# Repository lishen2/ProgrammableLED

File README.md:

自动刹车灯
===============
自动刹车灯是一个小巧的电路板，在刹车减速时自动亮起。可以将其安装在自行车上，用于警示其他车辆和行人。自动刹车灯由电池供电并内置加速度传感器，因此无需额外连接其他线缆。使用两节5号电池时，设计待机时间为一年以上(待机功耗66微安)，基本可以实现永不关机，即装即忘。项目命名为“ProgrammableLED”是最初的初衷，现在已经简化为自动刹车等了，功能简化体验更优。

特性
--------
* 体积2.8cm * 5.5cm(PCB尺寸)。
* 自动识别减速刹车。
* 停车自动休眠，设计待机时间一年以上。
* 软硬件设计开源。

应用
-------
* 自行车灯，提高车辆夜间识别度，增强安全性。

硬件资源
--------
* STM32F103C8T处理器
* 两个全彩LED灯，两个红色LED（1206）
* 加速度传感器ADXL345
* 一个三线串口
* 一个三线SWD接口

当前进度
--------
20140217: 第一版PCB制作完成.                     
20140220: 编写代码，STM32的USB驱动示例代码很烂，作为程序员不忍直视。              
20140319: 放弃使用USB口，原因是USB驱动比较复杂一直没有调试成功。                  
20140329: 第二版PCB制作完成，放弃USB接口，增加加速度传感器ADXL234和升压电路（保证LED亮度一致）                    
20140410：还在编写软件，放弃编程功能，仅留下刹车灯功能。                   
20140506：基本功能正常，正在优化功耗。
20140515：耗降到66微安，正在调整对加速度数值的处理。
20140601：加速度传感器参数调整完毕，经过几周实测，效果还不错。

开发博客
--------
<http://blog.sina.com.cn/lgeek>

Automatic Break Light
===============
Automatic Break Light is a small circuit board, it can automatically light up when decelerate. It can installed on a bicycle to caution other bicycle,  vehicle and people. Automatic Break Light has an accelerate sensor on board, so it will work without additional sensor or wire. It use two AA battery as power supply, designed to work at least 12 month(Standby power consumption is 66 uA). You no longer need to manually shut it down, and you can forget it after install. The project name "ProgrammableLED" is the original idea, but now it has enolved into "Automatic Break Light". Fewer functions, better experience.

Design feature
--------------
* size 2.8cm * 5.5cm(PCB size).
* recognize decelerate.
* automatic sleep when stop, standby lifetime more than 12 month.
* open source on both software and hardware.

Application
-----------
* Bicycle light, improve identification at night.

Hardware
--------
* STM32F103C8T MCU
* 2 RGB LED, 2 red LED
* ADXL345 acceleration sensor
* 1 USART port
* 1 SWD

Current progress
---------------
20140217: Finished first PCB.                
20140220: Working on the code, STM32's USB Driver is horrible.            
20140319: Abandon USB port, too complicated.         
20140329: Finished second PCB, abandon USB port, add ADXL234 sensor, and boost circuit.           
20140410：Still working on software, just break light.            
20140506：Barely work, working on reduce power consumption.
20140515：Standby power consumption down to 66 mA, Adjusting processing logic about acceleration value.
20140601: Finish adjusting logic. After several weeks trail, it's basically good.

Development blog
---------------
<http://lsgeek.blogspot.com>

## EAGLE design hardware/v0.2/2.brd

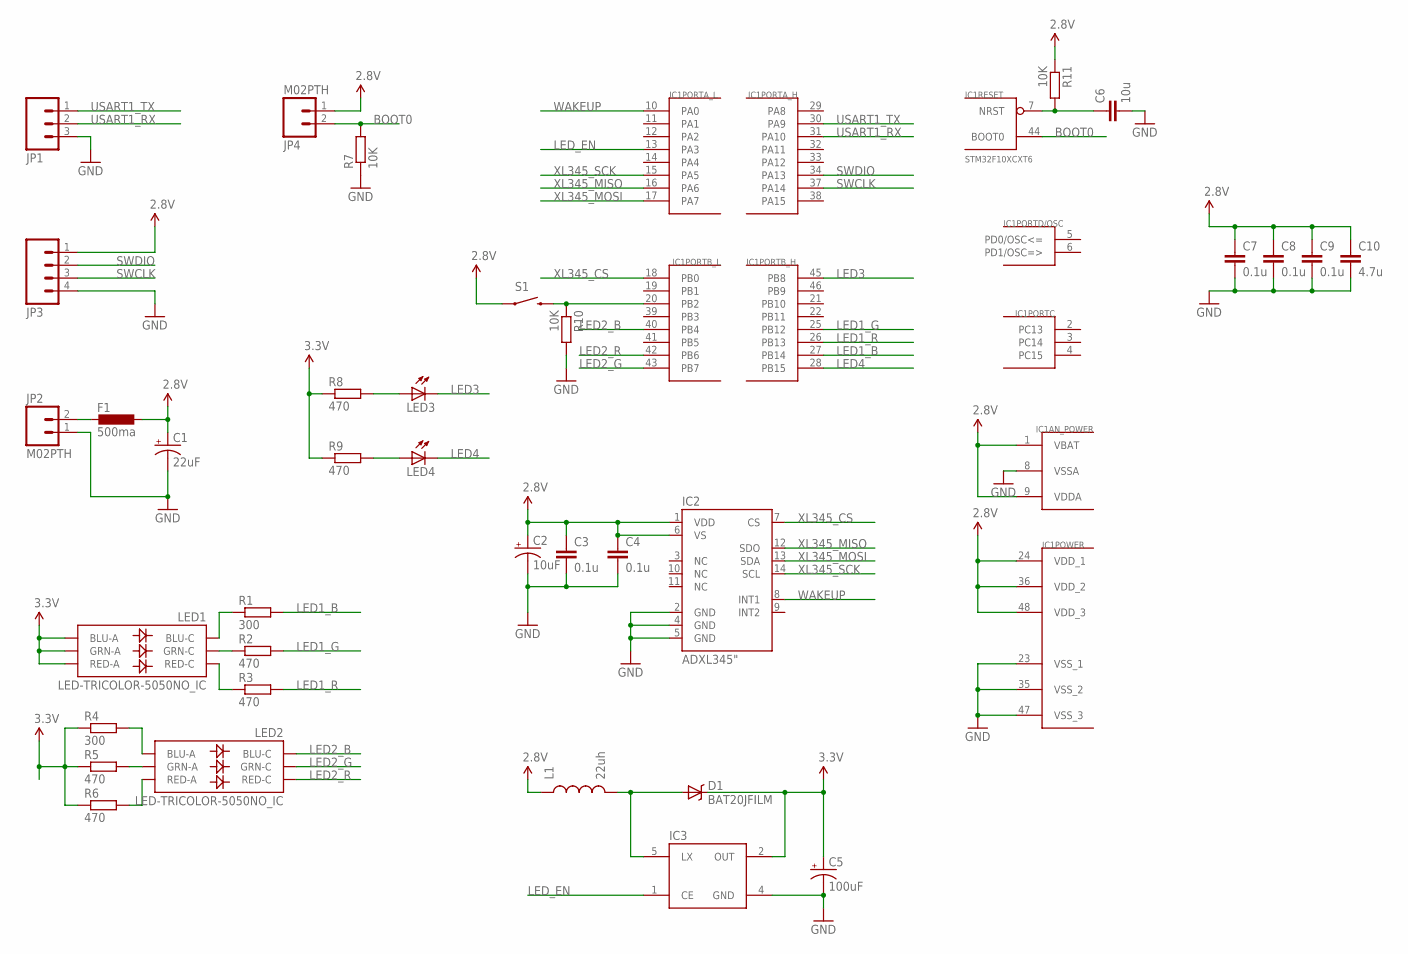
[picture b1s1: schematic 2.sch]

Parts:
C1: 22uF; EIA3216
C2: 10uF; EIA3216
C3, C4, C7, C8, C9: 0.1u; C0603K
C5: 100uF; EIA3528
C6: 10u; C0603K
C10: 4.7u; C0603K
D1: BAT20JFILM; SOD-323
F1: 500ma; L2012C
IC1: STM32F10XCXT6; TQFP48
IC2: ADXL345"; ADXL3451:1
IC3: BL8530-XX2_RN; SOT23-5
JP1: M03PTH; 1X03
JP2, JP4: M02PTH; 1X02
JP3: M04PTH; 1X04
L1: 22uh; VLF4012A
LED1, LED2: LED-TRICOLOR-5050NO_IC; LED-TRICOLOR-5050
LED3, LED4: LED1206; LED-1206
R1, R4: 300; R0603
R2, R3, R5, R6, R8, R9: 470; R0603
R7, R10, R11: 10K; R0603
S1: SWITCH-MOMENTARY-2-SMD-1101NE; TACTILE-SWITCH-1101NE

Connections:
2.8V: C1.A (+), C2.A (+), C3.1, C4.1, C7.1, C8.1, C9.1, C10.1, F1.1, IC1.1 (VBAT), IC1.9 (VDDA), IC1.24 (VDD_1), IC1.36 (VDD_2), IC1.48 (VDD_3), IC2.1 (VDD), IC2.6 (VS), JP3.1, JP4.1, L1.P$1 (1), R11.1, S1.P$1 (1)
3.3V: C5.A (+), D1.1 (C), IC3.2 (OUT), LED1.1 (GRN-A), LED1.2 (RED-A), LED1.3 (BLU-A), R4.1, R5.1, R6.1, R8.1, R9.1
BOOT0: IC1.44 (BOOT0), JP4.2, R7.2
GND: C1.C (-), C2.C (-), C3.2, C4.2, C5.C (-), C6.2, C7.2, C8.2, C9.2, C10.2, IC1.8 (VSSA), IC1.23 (VSS_1), IC1.35 (VSS_2), IC1.47 (VSS_3), IC2.2 (GND), IC2.4 (GND), IC2.5 (GND), IC3.4 (GND), JP1.3, JP2.1, JP3.4, R7.1, R10.2
LED1_B: IC1.27 (PB14), R1.2
LED1_G: IC1.25 (PB12), R2.2
LED1_R: IC1.26 (PB13), R3.2
LED2_B: IC1.40 (PB4), LED2.4 (BLU-C)
LED2_G: IC1.43 (PB7), LED2.6 (GRN-C)
LED2_R: IC1.42 (PB6), LED2.5 (RED-C)
LED3: IC1.45 (PB8), LED3.C
LED4: IC1.28 (PB15), LED4.C
LED_EN: IC1.13 (PA3), IC3.1 (CE)
unnamed: F1.2, JP2.2
unnamed: IC1.20 (PB2), R10.1, S1.P$2 (2)
unnamed: LED4.A, R9.2
unnamed: LED3.A, R8.2
unnamed: LED2.3 (BLU-A), R4.2
unnamed: LED1.6 (GRN-C), R2.1
unnamed: LED2.2 (RED-A), R6.2
unnamed: LED1.4 (BLU-C), R1.1
unnamed: LED2.1 (GRN-A), R5.2
unnamed: LED1.5 (RED-C), R3.1
unnamed: D1.2 (A), IC3.5 (LX), L1.P$2 (2)
RESET: C6.1, IC1.7 (NRST), R11.2
SWCLK: IC1.37 (PA14), JP3.3
SWDIO: IC1.34 (PA13), JP3.2
USART1_RX: IC1.31 (PA10), JP1.2
USART1_TX: IC1.30 (PA9), JP1.1
WAKEUP: IC1.10 (PA0), IC2.8 (INT1)
XL345_CS: IC1.18 (PB0), IC2.7 (CS)
XL345_MISO: IC1.16 (PA6), IC2.12 (SDO)
XL345_MOSI: IC1.17 (PA7), IC2.13 (SDA)
XL345_SCK: IC1.15 (PA5), IC2.14 (SCL)

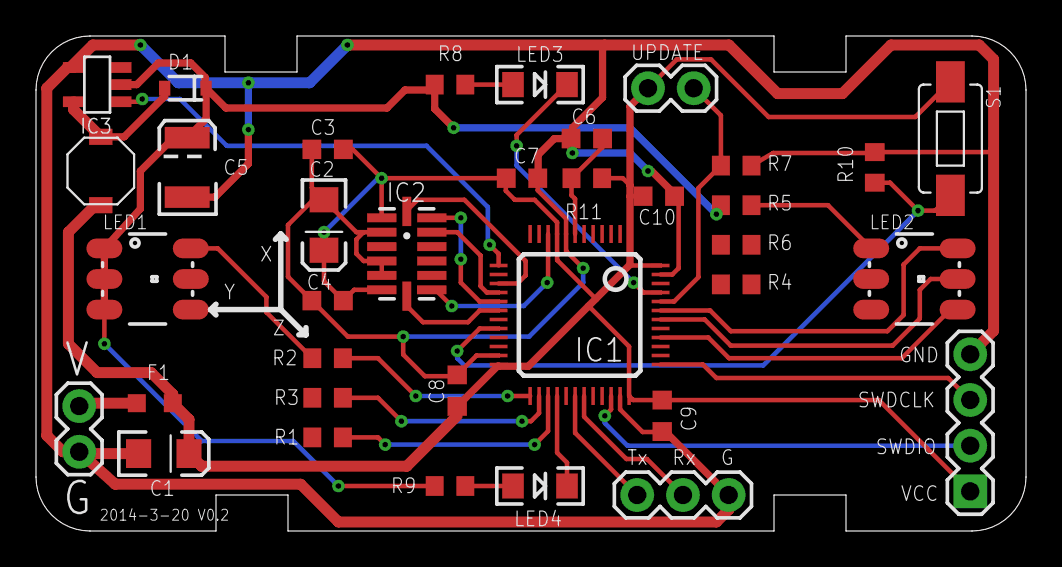
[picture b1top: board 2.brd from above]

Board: 2 copper layers, 55.0 x 27.5 mm, 36 parts (0 on the bottom side), 34 nets.

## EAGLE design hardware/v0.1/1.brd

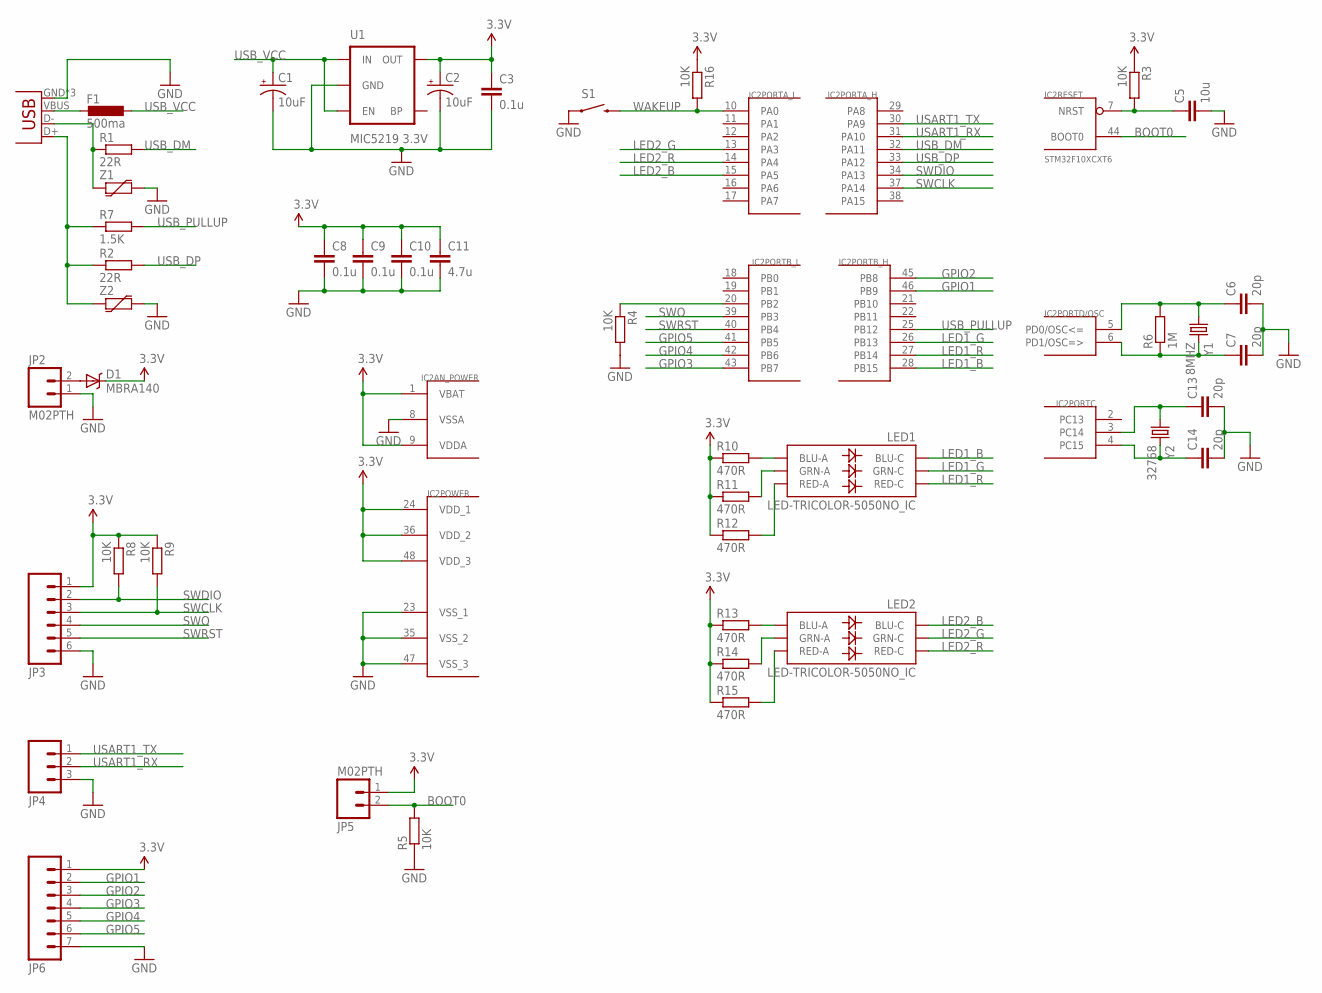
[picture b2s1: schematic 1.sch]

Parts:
C1, C2: 10uF; EIA3216
C3, C8, C9, C10: 0.1u; C0603K
C5: 10u; C0603K
C6, C7, C13, C14: 20p; C0603K
C11: 4.7u; C0603K
D1: MBRA140; SMA-DIODE
F1: 500ma; L2012C
IC2: STM32F10XCXT6; TQFP48
JP1: USB-MICROB
JP2, JP5: M02PTH; 1X02
JP3: M06SIP; 1X06
JP4: M03PTH; 1X03
JP6: M07; 1X07
LED1, LED2: LED-TRICOLOR-5050NO_IC; LED-TRICOLOR-5050
R1, R2: 22R; R0603
R3, R4, R5, R8, R9, R16: 10K; R0603
R6: 1M; R0603
R7: 1.5K; R0603
R10, R11, R12, R13, R14, R15: 470R; R0603
S1: SWITCH-MOMENTARY-2SMD-4; TACTILE_SWITCH_TALL
U1: MIC5219 3.3V; SOT23-5
Y1: 8MHZ; CRYSTAL-SMD-5X3
Y2: 32768; CRYSTAL-32KHZ-SMD_EPSON_MC146
Z1, Z2: VARISTOR-0603; 0603-RES

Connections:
3.3V: C2.A (+), C3.1, C8.1, C9.1, C10.1, C11.1, D1.C, IC2.1 (VBAT), IC2.9 (VDDA), IC2.24 (VDD_1), IC2.36 (VDD_2), IC2.48 (VDD_3), JP3.1, JP5.1, JP6.1, R3.1, R8.1, R9.1, R10.1, R11.1, R12.1, R13.1, R14.1, R15.1, R16.1, U1.5 (OUT)
BOOT0: IC2.44 (BOOT0), JP5.2, R5.2
GND: C1.C (-), C2.C (-), C3.2, C5.2, C6.2, C7.2, C8.2, C9.2, C10.2, C11.2, C13.2, C14.2, IC2.8 (VSSA), IC2.23 (VSS_1), IC2.35 (VSS_2), IC2.47 (VSS_3), JP1.GND, JP1.MT1 (GND), JP1.MT2 (GND), JP2.1, JP3.6, JP4.3, JP6.7, R4.2, R5.1, S1.A2 (1), U1.2 (GND), Z1.2, Z2.2
GPIO1: IC2.46 (PB9), JP6.2
GPIO2: IC2.45 (PB8), JP6.3
GPIO3: IC2.43 (PB7), JP6.4
GPIO4: IC2.42 (PB6), JP6.5
GPIO5: IC2.41 (PB5), JP6.6
LED1_B: IC2.28 (PB15), LED1.4 (BLU-C)
LED1_G: IC2.26 (PB13), LED1.6 (GRN-C)
LED1_R: IC2.27 (PB14), LED1.5 (RED-C)
LED2_B: IC2.15 (PA5), LED2.4 (BLU-C)
LED2_G: IC2.13 (PA3), LED2.6 (GRN-C)
LED2_R: IC2.14 (PA4), LED2.5 (RED-C)
unnamed: D1.A, JP2.2
unnamed: IC2.20 (PB2), R4.1
unnamed: JP1.D-, R1.1, Z1.1
unnamed: JP1.D+, R2.1, R7.1, Z2.1
unnamed: C6.1, IC2.5 (PD0/OSC<=), R6.2, Y1.1
unnamed: C7.1, IC2.6 (PD1/OSC=>), R6.1, Y1.3 (2)
unnamed: LED1.3 (BLU-A), R10.2
unnamed: F1.2, JP1.VBUS
unnamed: LED1.1 (GRN-A), R11.2
unnamed: LED1.2 (RED-A), R12.2
unnamed: LED2.3 (BLU-A), R13.2
unnamed: LED2.1 (GRN-A), R14.2
unnamed: LED2.2 (RED-A), R15.2
unnamed: C13.1, IC2.3 (PC14), Y2.P$2 (1)
unnamed: C14.1, IC2.4 (PC15), Y2.P$1 (2)
RESET: C5.1, IC2.7 (NRST), R3.2
SWCLK: IC2.37 (PA14), JP3.3, R9.2
SWDIO: IC2.34 (PA13), JP3.2, R8.2
SWO: IC2.39 (PB3), JP3.4
SWRST: IC2.40 (PB4), JP3.5
USART1_RX: IC2.31 (PA10), JP4.2
USART1_TX: IC2.30 (PA9), JP4.1
USB_DM: IC2.32 (PA11), R1.2
USB_DP: IC2.33 (PA12), R2.2
USB_PULLUP: IC2.25 (PB12), R7.2
USB_VCC: C1.A (+), F1.1, U1.1 (IN), U1.3 (EN)
WAKEUP: IC2.10 (PA0), R16.2, S1.B2 (2)

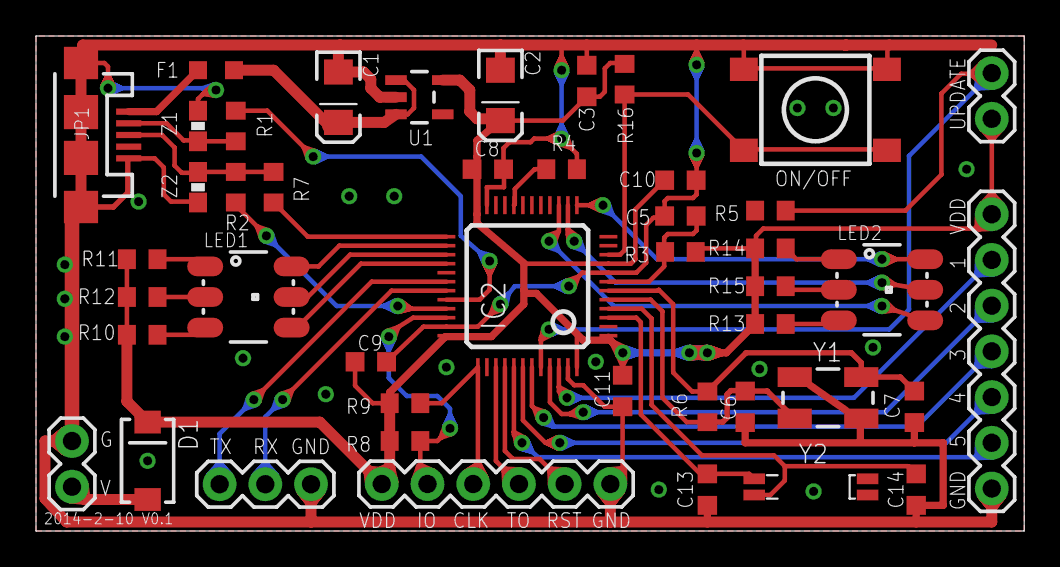
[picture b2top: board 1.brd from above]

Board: 2 copper layers, 54.9 x 27.5 mm, 45 parts (0 on the bottom side), 41 nets.

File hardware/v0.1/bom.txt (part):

Partlist exported from C:/Documents and Settings/Administrator/eagle/SmartLED/1.sch at 2014-2-13 17:03:51

Part Value                   Device                  Package                       Description                                                                         PROD_ID    VALUE       
C1   10uF                    10UF-TANT               EIA3216                       10uF Tantalum SMT                                                                   CAP-00811  10uF        
C2   10uF                    10UF-TANT               EIA3216                       10uF Tantalum SMT                                                                   CAP-00811  10uF        
C3   0.1u                    C-EUC0603K              C0603K                        CAPACITOR, European symbol                                                                                 
C5   10u                     C-EUC0603K              C0603K                        CAPACITOR, European symbol                                                                                 
C6   20p                     C-EUC0603K              C0603K                        CAPACITOR, European symbol                                                                                 
C7   20p                     C-EUC0603K              C0603K                        CAPACITOR, European symbol                                                                                 
C8   0.1u                    C-EUC0603K              C0603K                        CAPACITOR, European symbol                                                                                 
C9   0.1u                    C-EUC0603K              C0603K                        CAPACITOR, European symbol                                                                                 
C10  0.1u                    C-EUC0603K              C0603K                        CAPACITOR, European symbol                                                                                 
C11  4.7u                    C-EUC0603K              C0603K                        CAPACITOR, European symbol                                                                                 
C13  20p                     C-EUC0603K              C0603K                        CAPACITOR, European symbol                                                                                 
C14  20p                     C-EUC0603K              C0603K                        CAPACITOR, European symbol                                                                                 
D1   MBRA140                 MBRA140                 SMA-DIODE                     40V, 1A Schottky rectifier                                                          DIO-08053              
F1   500ma                   L-EUL2012C              L2012C                        INDUCTOR, European symbol                                                                                  
IC2  STM32F10XCXT6           STM32F10XCXT6           TQFP48                        ST STM32F101/103 48pin LQFP                                                                                
JP1  USB-MICROB              USB-MICROB              USB-MICROB                    USB Connectors                                                                      CONN-09505             
JP2  M02PTH                  M02PTH                  1X02                          Standard 2-pin 0.1" header. Use with                                                                       
JP3                          M06SIP                  1X06                          Header 6                                                                                                   
JP4                          M03PTH                  1X03                          Header 3                                                                                                   
JP5  M02PTH                  M02PTH                  1X02                          Standard 2-pin 0.1" header. Use with                                                                       
JP6                          M07                     1X07                          Header 7                                                                                                   
LED1 LED-TRICOLOR-5050NO_IC  LED-TRICOLOR-5050NO_IC  LED-TRICOLOR-5050                                                                                                                        
LED2 LED-TRICOLOR-5050NO_IC  LED-TRICOLOR-5050NO_IC  LED-TRICOLOR-5050                                                                                                                        
R1   22R                     R-EU_R0603              R0603                         RESISTOR, European symbol                                                                                  
R2   22R                     R-EU_R0603              R0603                         RESISTOR, European symbol                                                                                  
R3   10K                     R-EU_R0603              R0603                         RESISTOR, European symbol                                                                                  
R4   10K                     R-EU_R0603              R0603                         RESISTOR, European symbol                                                                                  
R5   10K                     R-EU_R0603              R0603                         RESISTOR, European symbol                                                                                  
R6   1M                      R-EU_R0603              R0603                         RESISTOR, European symbol                                                                                  
R7   1.5K                    R-EU_R0603              R0603                         RESISTOR, European symbol                                                                                  
R8   10K                     R-EU_R0603              R0603                         RESISTOR, European symbol                                                                                  
R9   10K                     R-EU_R0603              R0603                         RESISTOR, European symbol                                                                                  
R10  470R                    R-EU_R0603              R0603                         RESISTOR, European symbol                                                                                  
R11  470R                    R-EU_R0603              R0603                         RESISTOR, European symbol                                                                                  
R12  470R                    R-EU_R0603              R0603                         RESISTOR, European symbol                                                                                  
R13  470R                    R-EU_R0603              R0603                         RESISTOR, European symbol                                                                                  
R14  470R                    R-EU_R0603              R0603                         RESISTOR, European symbol                                                                                  
R15  470R                    R-EU_R0603              R0603                         RESISTOR, European symbol                                                                                  
R16  10K                     R-EU_R0603              R0603                         RESISTOR, European symbol                                                                                  
S1   SWITCH-MOMENTARY-2SMD-4 SWITCH-MOMENTARY-2SMD-4 TACTILE_SWITCH_TALL           Various NO switches- pushbuttons, reed, etc                                                                
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
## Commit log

2014-02-13 update readme, commit pcb design
2014-02-14 add jdbpcb cam file
2014-02-18 Update readme.md, fix a minor bug on PCB
2014-02-18 add software
2014-02-18 add image
2014-02-18 update image
2014-02-18 make readme display image
2014-02-20 Add test code
2014-02-20 更新进度
2014-02-21 update usb driver
2014-02-23 makeing standard request work
2014-02-24 continue development usb driver
2014-02-26 fix a bug, which is issued when recived multiple CTR interupts on EP0
2014-02-27 1. devided usb into usb library files and usb user files. 2.Begin to write scsi related code.
2014-03-02 writing usb driver
2014-03-04 implement SCSI inquery command, but have problems
2014-03-05 bulk endpoint get babble error when transmit data, not yet figure it out.
2014-03-12 add code read adxl345 chip
2014-03-14 write display control code
2014-03-16 add version 2 pcb desgin
2014-03-16 add xl345 code and flash control
2014-03-17 modify pcb design
2014-03-18 test led pwm alg
2014-03-19 Updated V2 PCB design
2014-03-20 update PCB design
2014-03-20 nearly finish PCB design
2014-03-24 finish version 0.2 pcb design
2014-03-26 testing flash display sequence
2014-03-27 20140327
2014-03-31 temp 20140331
2014-03-31 temporary
2014-04-02 update xl345 code
2014-04-03 update xl345
2014-04-07 adapt new hardware
2014-04-08 temp
2014-04-09 ACC now work properly
2014-04-10 nearly finish
2014-04-10 add space
2014-04-10 correct compile error
2014-05-03 workable version 1
2014-05-04 update schematic for clearance
2014-05-05 reduce standby power
2014-05-05 improve power consumion
2014-05-06 update readme and image
2014-05-06 reduce power consumption
2014-05-06 achieve 66 uA standby power consumption
2014-05-08 improve break light sensitivity
2014-05-11 fix a bug: device won't sleep
2014-05-13 update display logic
2014-05-16 修改readme;升级加速度数据处理逻辑
2014-05-16 update color
2014-05-20 update acc sensor parameter
2015-09-12 update layout

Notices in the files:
parts and their libraries:
SparkFun-Connectors: Licensing: CC v3.0 Share-Alike You are welcome to use this library for commercial purposes.
